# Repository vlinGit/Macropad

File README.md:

<h1 align="center"> Macropad </h1>

## Table of Contents
* [Introduction](#introduction)
* [Macropad](#macropad)
    * [Schematic](#schematic)
    * [PCB](#pcb)
    * [Parts](#parts)
* [Firmware](#firmware)
    * [Default mode](#default-mode)
    * [Function mode](#function-mode)
* [Future plans](#future-plans)

<hr>

## Introduction

Greetings, It seems you've stubbled upon my macropad project :)!
Utilizing everything provided from this repo (with a few exceptions) you should be able to make this simple 4x4 macropad using a Pi Pico:

Now I must set some ground rules and mentions those exceptions from the previous text. 
This repo assumes you have knowledge of:

* [Python](https://www.python.org/)
* [Kicad](https://www.kicad.org/)
* [CircuitPython](https://circuitpython.org/) - This should be installed on your Pi Pico

The next two sections will discuss what the two folders, Macropad and Firmware, in this project do.
<hr>

## Macropad

All the project files (schematic, pcb, and fingerprints) should be in this folder. When opening this within Kicad, you will most likely need to reassign the location of the fingerprints.

##### Schematic:

##### PCB:

##### Parts:
* 16 Kahlil hotswap sockets
* 1 Raspberry Pi Pico
* 16 SMD Diodes
* Header pins for the pico (optional)
* Micro usb wire
* Soldering kit

Here's a [spreadsheet](https://docs.google.com/spreadsheets/d/1NUBolih80QTXxrNlfvGj-lknc-THMJnu64dy0pHb7lM/edit?usp=sharing) containing all the items I used. This spreadsheet doesn't include headers, switches, and keys as I already had these lying around.

<i><b>Sidenote</b>, I left a place for a reset button for convinence, however, this proved to be the complete opposite. The small button got in the way more often than not so the final build doesn't include it. </i>

<hr>

## Firmware

You will find a <b>lib</b> folder as well as a <b>code.py</b> file in here. The <b>lib</b> folder contains the necessary adafruit library needed for the python file <b>code.py</b> which contains the actual firmware code. These files should be dragged into your Pi Pico after you've installed CircuitPython.

The macropad is designed in a 4x4 matrix with the following pins:

* Rows: GP21, GP20, GP19, GP18
* Columns: GP6, GP7, GP8, GP9

The current python file provides you with two modes:
1. [Default mode](#default-mode) - for media controls
2. [Function mode](#function-mode) - for general purpose binds using F13-F21 keys, mainly for binding macros in software (blender, kritia, etc.)

The modes will be presented in tables, each cell being a key. Every cell labeled <i>null</i> means the key is unassigned. Within the actual code this is represented with a -1.

##### Default Mode:

<table>
    <tr>
        <td>VOLUME DECREMENT</td>
        <td>VOLUME INCREMENT</td>
        <td>MUTE VOLUME</td>
        <td>CHANGE MODE</td>
    </tr>
    <tr>
        <td>PREVIOUS TRACK</td>
        <td>PLAY/PAUSE MEDIA</td>
        <td>NEXT TRACK</td>
        <td><i>null</i></td>
    </tr>
    <tr>
        <td><i>null</i></td>
        <td><i>null</i></td>
        <td><i>null</i></td>
        <td><i>null</i></td>
    </tr>
    <tr>
        <td><i>null</i></td>
        <td><i>null</i></td>
        <td><i>null</i></td>
        <td><i>null</i></td>
    </tr>
</table>

##### Function Mode:

<table>
    <tr>
        <td>LEFT SHIFT</td>
        <td>F14</td>
        <td>F15</td>
        <td>CHANGE MODE</td>
    </tr>
    <tr>
        <td>F13</td>
        <td>F17</td>
        <td>F18</td>
        <td>F19</td>
    </tr>
    <tr>
        <td>F16</td>
        <td>F21</td>
        <td>F22</td>
        <td>F23</td>
    </tr>
    <tr>
        <td>LEFT CONTROL</td>
        <td>F20</td>
        <td><i>null</i></td>
        <td>SPACE</td>
    </tr>
</table>

<hr>

## Future plans

So, whats planned for the future? I've been using this macropad for a couple days now and here's the following things I plan on implementing soon:

1. <b>Proper case</b> - I've created the model, but now just need to get a 3D printer and do some troubleshooting
2. <b>Rotary Encoders</b> - Will be great for volume control and zooming in
3. <b>Standalone LED + Mode button</b> - Just for mode switching
4. <b>IR Sensors</b> - Really looking forward to this one! Plan on adding AC and table height controls using this.

As to what I will remove:
1. <b>The reset button</b> - Honestly made it less comfortable to use
2. <b>Micro usb</b>- Looking to replace this with a USB-C port

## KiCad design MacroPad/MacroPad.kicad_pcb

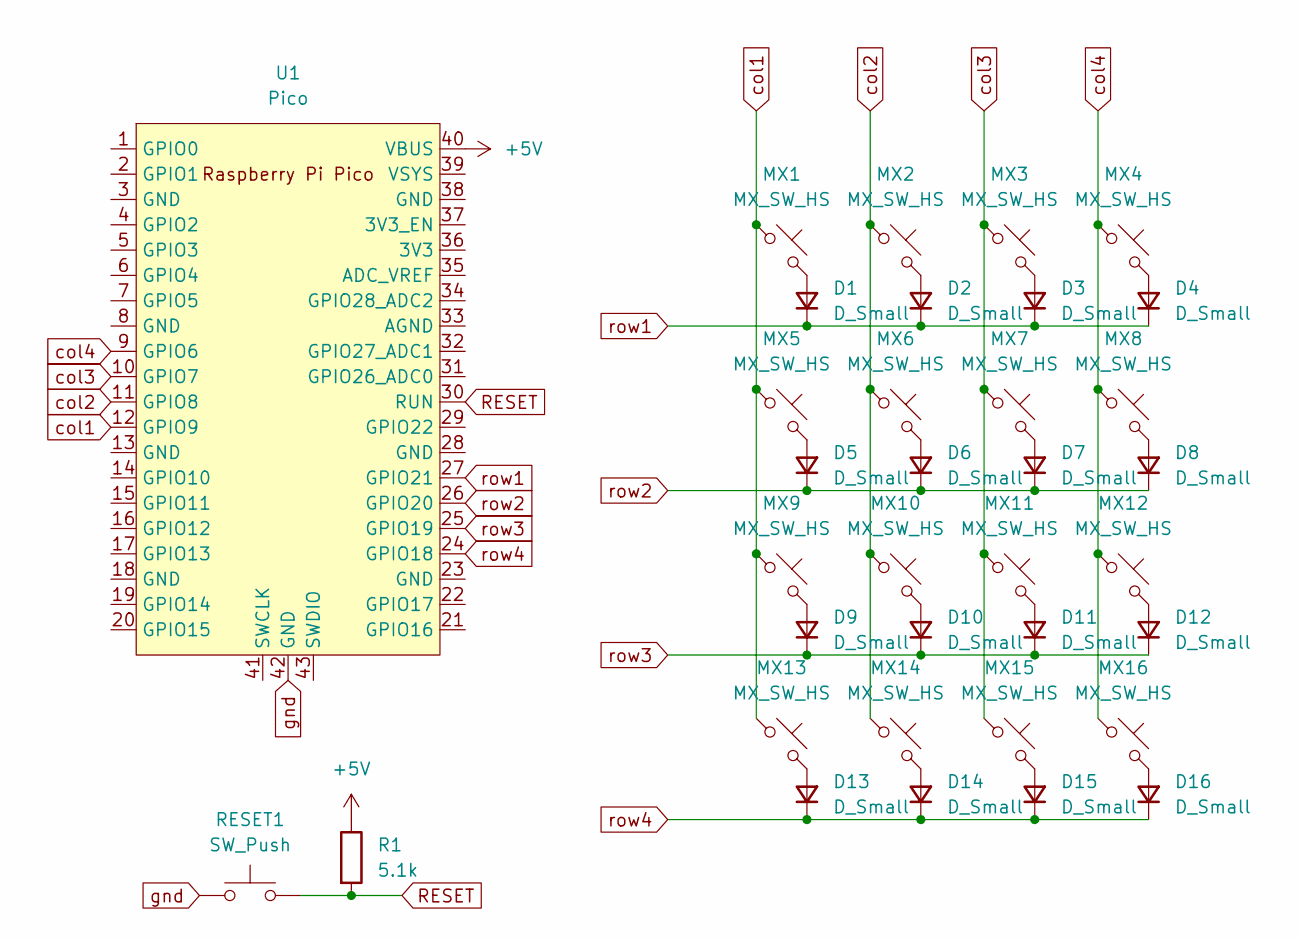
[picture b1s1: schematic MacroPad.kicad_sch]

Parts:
D1, D2, D3, D4, D5, D6, D7, D8, D9, D10, D11, D12, D13, D14, D15, D16: D_Small; D_SOD-123
MX1, MX2, MX3, MX4, MX5, MX6, MX7, MX8, MX9, MX10, MX11, MX12, MX13, MX14, MX15, MX16: MX_SW_HS; SW_MX_HS_CPG151101S11_1u
R1: 5.1k; R_0805_2012Metric_Pad1.20x1.40mm_HandSolder
RESET1: SW_Push; SW_SPST_PTS645
U1: Pico; RPi_Pico_SMD_TH

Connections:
+5V: R1.1, U1.40 (VBUS)
unnamed: D1.2 (A), MX1.2
unnamed: D2.2 (A), MX2.2
unnamed: D3.2 (A), MX3.2
unnamed: D4.2 (A), MX4.2
unnamed: D5.2 (A), MX5.2
unnamed: D6.2 (A), MX6.2
unnamed: D7.2 (A), MX7.2
unnamed: D8.2 (A), MX8.2
unnamed: D9.2 (A), MX9.2
unnamed: D10.2 (A), MX10.2
unnamed: D11.2 (A), MX11.2
unnamed: D12.2 (A), MX12.2
unnamed: D13.2 (A), MX13.2
unnamed: D14.2 (A), MX14.2
unnamed: D15.2 (A), MX15.2
unnamed: D16.2 (A), MX16.2
RESET: R1.2, RESET1.2, U1.30 (RUN); also elsewhere on the board
col1: MX1.1, MX5.1, MX9.1, MX13.1, U1.12 (GPIO9)
col2: MX2.1, MX6.1, MX10.1, MX14.1, U1.11 (GPIO8)
col3: MX3.1, MX7.1, MX11.1, MX15.1, U1.10 (GPIO7)
col4: MX4.1, MX8.1, MX12.1, MX16.1, U1.9 (GPIO6)
gnd: RESET1.1, U1.42 (GND); also elsewhere on the board
row1: D1.1 (K), D2.1 (K), D3.1 (K), D4.1 (K), U1.27 (GPIO21)
row2: D5.1 (K), D6.1 (K), D7.1 (K), D8.1 (K), U1.26 (GPIO20)
row3: D9.1 (K), D10.1 (K), D11.1 (K), D12.1 (K), U1.25 (GPIO19)
row4: D13.1 (K), D14.1 (K), D15.1 (K), D16.1 (K), U1.24 (GPIO18)

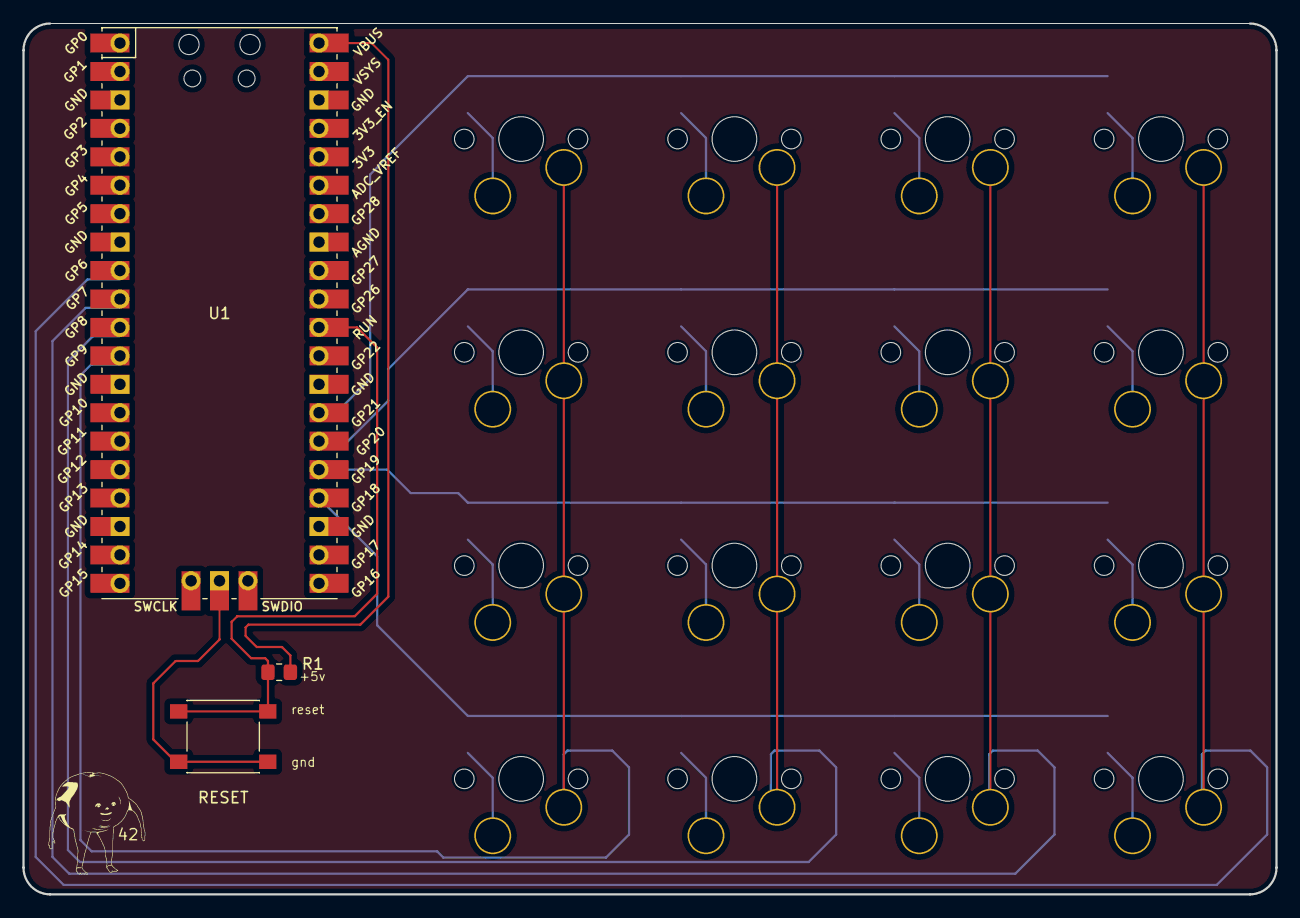
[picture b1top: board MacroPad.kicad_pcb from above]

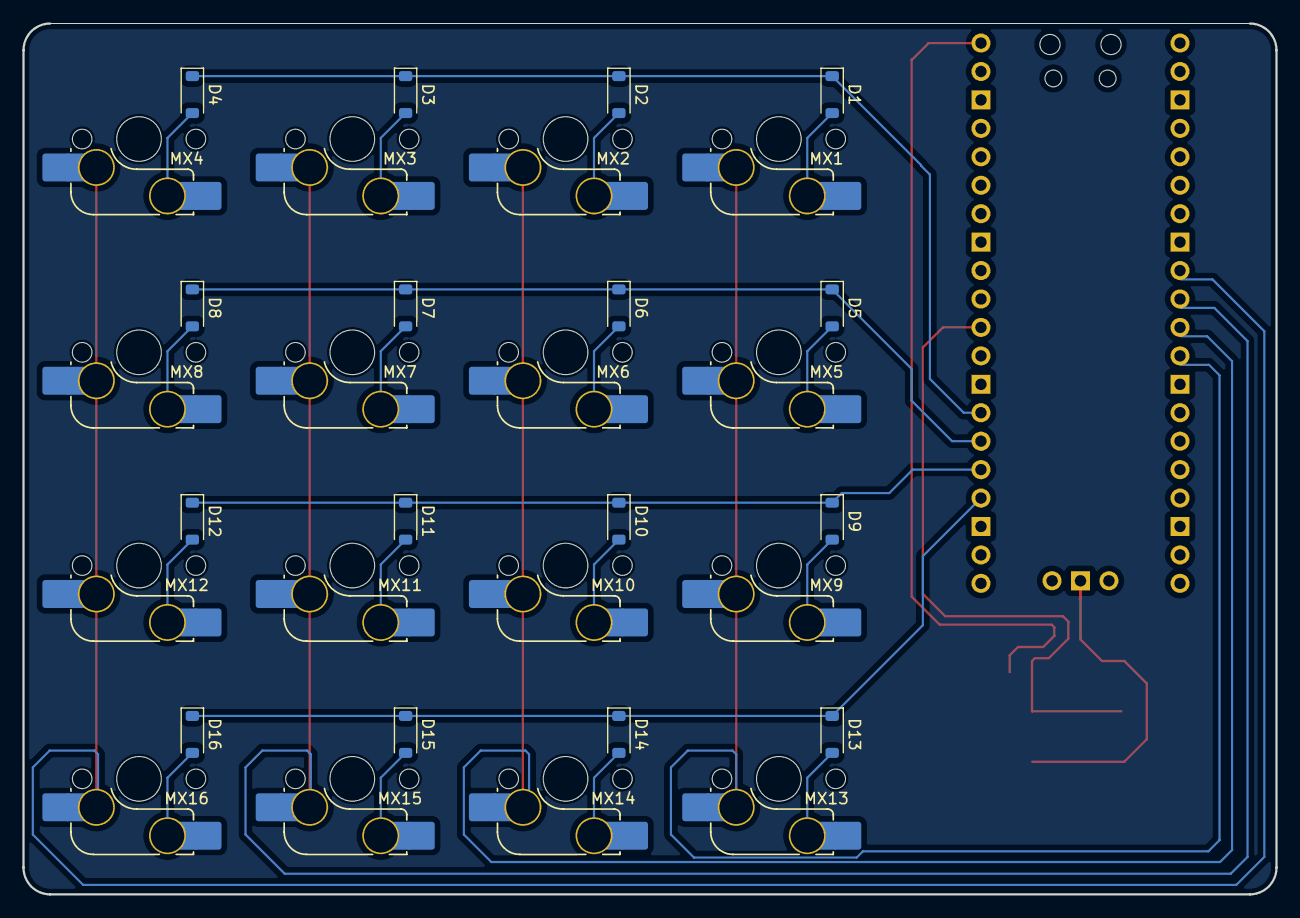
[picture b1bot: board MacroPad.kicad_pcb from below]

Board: 2 copper layers, 111.9 x 77.8 mm, 36 parts (32 on the bottom side), 27 nets.

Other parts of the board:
42: LOGO
RESET: SW_Push; SW_SPST_PTS645

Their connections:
RESET: RESET.2; also elsewhere on the board
gnd: RESET.1; also elsewhere on the board

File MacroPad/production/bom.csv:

Designator,Footprint,Quantity,Value,LCSC Part #
"D1, D10, D11, D12, D13, D14, D15, D16, D2, D3, D4, D5, D6, D7, D8, D9",D_SOD-123,16,D_Small,
"MX1, MX10, MX11, MX12, MX13, MX14, MX15, MX16, MX2, MX3, MX4, MX5, MX6, MX7, MX8, MX9",SW_MX_HS_CPG151101S11_1u,16,MX_SW_HS,
R1,0805,1,5.1k,
RESET,SW_SPST_PTS645,1,SW_Push,
U1,RPi_Pico_SMD_TH,1,Pico,

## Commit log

2024-05-07 readme file
2024-05-07 fixed an image path typo
